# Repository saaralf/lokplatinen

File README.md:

ErsatzPlatine für Fleischmann 7333 BR 110

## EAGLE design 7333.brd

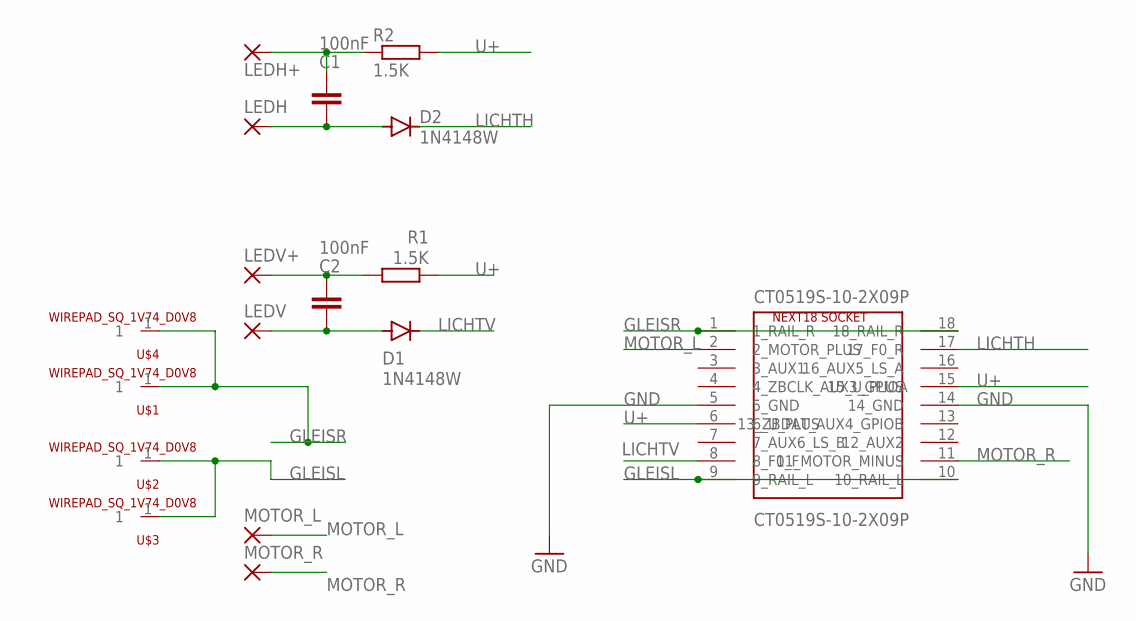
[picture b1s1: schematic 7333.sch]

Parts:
C1, C2: 100nF; C0805
CT0519S-10-2X09P: CT0519S-10-2X09P; NEXT18_SOCKET_GENERIC_VERIFY
D1, D2: 1N4148W; SOD123
LEDH: SMD2; SMD1,27-2,54
LEDH+: SMD2; SMD1,27-2,54
LEDV: SMD2; SMD1,27-2,54
LEDV+: SMD2; SMD1,27-2,54
MOTOR_L: SMD5; SMD2,54-5,08
MOTOR_R: SMD5; SMD2,54-5,08
R1, R2: 1.5K; M0805
U$1, U$2, U$3, U$4: WIREPAD_SQ_1V74_D0V8

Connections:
GLEISL: CT0519S-10-2X09P.9 (9_RAIL_L), CT0519S-10-2X09P.10 (10_RAIL_L), U$2.1, U$3.1
GLEISR: CT0519S-10-2X09P.1 (1_RAIL_R), CT0519S-10-2X09P.18 (18_RAIL_R), U$1.1, U$4.1
GND: CT0519S-10-2X09P.5 (5_GND), CT0519S-10-2X09P.14 (14_GND)
LICHTH: CT0519S-10-2X09P.17 (17_F0_R), D2.C
LICHTV: CT0519S-10-2X09P.8 (8_F0_F), D1.C
MOTOR_L: CT0519S-10-2X09P.2 (2_MOTOR_PLUS), MOTOR_L.1
MOTOR_R: CT0519S-10-2X09P.11 (11_MOTOR_MINUS), MOTOR_R.1
unnamed: C1.1, LEDH+.1, R2.1
unnamed: C2.2, D1.A, LEDV.1
unnamed: C2.1, LEDV+.1, R1.2
unnamed: C1.2, D2.A, LEDH.1
U+: CT0519S-10-2X09P.6 (6_U_PLUS), CT0519S-10-2X09P.15 (15_U_PLUS), R1.1, R2.2

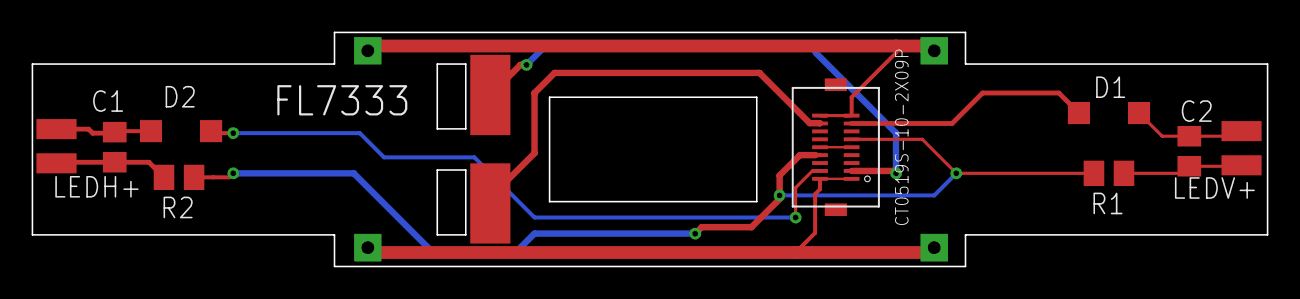
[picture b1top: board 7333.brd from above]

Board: 2 copper layers, 78.1 x 14.8 mm, 17 parts (0 on the bottom side), 12 nets.

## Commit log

2026-01-03 Platine für Fleischmann 7333 BR 110
2026-01-03 Add project title to README
2026-01-03 Add image to README for Fleischmann 7333 BR 110
    Added an image to the README file.
2026-01-03 EASYEDA Project für FL 7375 hiunzugefügt
2026-01-03 Add additional image to README
2026-05-18 Initial import of LokPlatinen
2026-05-18 Add .gitignore for EAGLE backup/temp files
2026-05-18 next18 namen
2026-05-18 Bild hinzugefügt
2026-05-18 Add additional image to README.md
